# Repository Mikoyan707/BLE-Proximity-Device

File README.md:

# ESP32-C3 BLE Proximity Device

A two-node Bluetooth Low Energy (BLE) proximity detection system based on the **ESP32-C3**, designed to detect when two dedicated devices come within a defined proximity range.

The project combines a custom-designed PCB with ESP32-C3 BLE communication and an RSSI-based proximity detection algorithm. Each device continuously scans for its counterpart and uses the received BLE signal strength to determine whether the other device has entered the configured proximity region.

> **Project Status:** Hardware design completed. Firmware development, RSSI calibration, and physical testing are in progress.

---

## Overview

The system consists of two identical BLE-enabled devices.

Each device:

1. Advertises its BLE identity.
2. Continuously scans for the corresponding device.
3. Detects the other device when its BLE advertisement is received.
4. Measures the received signal strength indicator (RSSI).
5. Filters the RSSI measurements to reduce short-term fluctuations.
6. Applies a configurable proximity threshold.
7. Activates the local output when the other device enters the defined proximity region.

The system is intended to operate without requiring a smartphone or external gateway.

### Basic Concept

```text
             BLE Proximity Link

        Device A                 Device B
     ┌─────────────┐          ┌─────────────┐
     │ ESP32-C3    │          │ ESP32-C3    │
     │             │          │             │
     │ Advertise   │◄────────►│ Advertise   │
     │ Scan        │   BLE    │ Scan        │
     │ RSSI        │          │ RSSI        │
     │ Processing  │          │ Processing  │
     └──────┬──────┘          └──────┬──────┘
            │                        │
            ▼                        ▼
         Output                   Output
```

---

## Key Features

* Two-node standalone BLE proximity system
* ESP32-C3 based design
* BLE advertising and scanning
* Dedicated device identification
* RSSI-based proximity estimation
* RSSI filtering for improved stability
* Configurable proximity threshold
* Hysteresis-based proximity decision
* Custom PCB designed in KiCad
* CR2032 battery-powered hardware design
* 3.3 V regulated power supply
* Local LED/output indication
* Firmware structured for future expansion

---

## Hardware

The custom PCB is built around the **ESP32-C3-MINI-1-N4** module.

### Main Hardware

| Component             | Function                                        |
| --------------------- | ----------------------------------------------- |
| ESP32-C3-MINI-1-N4    | Main MCU and BLE controller                     |
| CR2032                | Battery supply                                  |
| AP2112K-3.3           | 3.3 V voltage regulator                         |
| LED                   | Proximity/status indication                     |
| Transistor stage      | LED/output driving                              |
| Push buttons          | User/control input                              |
| Decoupling capacitors | Power supply stabilization                      |
| Resistors             | Pull-ups, current limiting and transistor drive |

The complete schematic and PCB design are available in the [`hardware`](hardware/) directory.

---

## Hardware Design

### Schematic

The complete KiCad schematic is available at:

```text
hardware/schematic/
```

The repository will contain both the editable KiCad schematic and an exported version for easy viewing.

### PCB

The PCB has been designed specifically for the ESP32-C3 based proximity device.

```text
hardware/pcb/
```

The directory contains the editable PCB design and exported PCB views.

### 3D Design

3D renders of the PCB are provided in:

```text
hardware/3d/
```

These views are intended to document the physical board layout and component placement.

---

## Proximity Detection

The system uses **BLE RSSI** as an indicator of relative proximity.

A simplified detection pipeline is:

```text
BLE Advertisement
        │
        ▼
Device Identification
        │
        ▼
RSSI Measurement
        │
        ▼
RSSI Filtering
        │
        ▼
Proximity Decision
        │
    ┌───┴───┐
    ▼       ▼
   NEAR     FAR
    │       │
    ▼       ▼
 Output   Output
   ON       OFF
```

RSSI is not treated as an exact distance measurement because it is affected by antenna orientation, obstacles, multipath propagation, human-body absorption, and the surrounding environment.

Therefore, the project will use experimental calibration to determine a suitable operating threshold for the intended application.

---

## Firmware

Firmware development is currently in progress.

The planned firmware architecture consists of separate modules for:

```text
firmware/
├── src/
│   ├── main.cpp
│   ├── ble_proximity.cpp
│   ├── ble_proximity.h
│   ├── proximity.cpp
│   ├── proximity.h
│   ├── led.cpp
│   ├── led.h
│   └── config.h
│
└── platformio.ini
```

The firmware will progressively implement:

* GPIO initialization
* Output/LED control
* BLE advertising
* BLE scanning
* Device identification
* RSSI acquisition
* RSSI filtering
* Proximity state detection
* Hysteresis
* Timing/debounce logic
* Final proximity indication

---

## RSSI Filtering

Raw RSSI measurements can fluctuate considerably even when two devices remain stationary.

For this reason, the firmware will process multiple RSSI measurements rather than making a proximity decision from a single sample.

The planned processing chain is:

```text
Raw RSSI
   │
   ▼
Filtering
   │
   ▼
Filtered RSSI
   │
   ▼
Threshold + Hysteresis
   │
   ▼
Proximity State
```

The filtering method and threshold values will be finalized after measurements are collected from the actual hardware.

---

## Calibration

The proximity threshold will be experimentally determined using the completed devices.

Measurements will be collected at different physical separations and under different orientations.

Example measurement format:

| Distance | RSSI |
| -------: | ---: |
|    0.5 m |  TBD |
|    1.0 m |  TBD |
|    1.5 m |  TBD |
|    2.0 m |  TBD |
|    3.0 m |  TBD |
|    4.0 m |  TBD |

These values will be replaced with measurements from the physical hardware.

Detailed calibration results will be documented in:

```text
documentation/RSSI_calibration.md
```

---

## Repository Structure

```text
ESP32-C3-BLE-Proximity/
│
├── README.md
├── LICENSE
│
├── hardware/
│   ├── schematic/
│   ├── pcb/
│   ├── 3d/
│   └── fabrication/
│
├── firmware/
│   ├── src/
│   └── test/
│
├── documentation/
│
├── images/
│
└── results/
```

---

## Development Roadmap

### Hardware

* [ ] Schematic design
* [ ] PCB layout
* [ ] 3D PCB design/review
* [ ] PCB fabrication
* [ ] Physical hardware assembly
* [ ] Hardware validation

### Firmware

* [ ] GPIO test
* [ ] BLE advertising
* [ ] BLE scanning
* [ ] Device identification
* [ ] RSSI measurement
* [ ] RSSI filtering
* [ ] Proximity threshold
* [ ] Hysteresis
* [ ] LED/output control
* [ ] Two-device testing
* [ ] Final firmware optimization

### Documentation

* [ ] Initial hardware documentation
* [ ] Firmware architecture
* [ ] BLE protocol documentation
* [ ] RSSI calibration
* [ ] Experimental results
* [ ] Final performance analysis

---

## Limitations

The primary proximity estimation method is based on BLE RSSI.

RSSI-based proximity estimation does not provide a universally accurate physical distance because the measured signal strength depends on the environment and device orientation.

Potential sources of variation include:

* Antenna orientation
* Obstacles
* Human-body effects
* Multipath propagation
* Reflections
* Transmit power
* Device-to-device orientation
* Environmental RF interference

The final operating threshold will therefore be selected experimentally rather than assuming a fixed RSSI-to-distance relationship.

---

## Future Improvements

Potential future developments include:

* Improved RSSI filtering
* Adaptive proximity thresholds
* Low-power BLE operation
* Battery-life optimization
* Improved proximity-state stability
* Additional user feedback mechanisms
* Enclosure design
* More extensive environmental testing
* Multiple proximity zones
* Improved ranging techniques beyond basic RSSI

---

## Tools Used

* **KiCad** — Schematic and PCB design
* **ESP32-C3** — Embedded controller and BLE
* **PlatformIO / Arduino framework** — firmware development
* **Git / GitHub** — Version control and project documentation

---

## Project Status

This project is under active development.

The custom hardware design is being documented first, followed by firmware implementation, RSSI calibration, physical testing, and final performance evaluation.

---

## License

This project is released under the **MIT License**.

See `LICENSE` for details.

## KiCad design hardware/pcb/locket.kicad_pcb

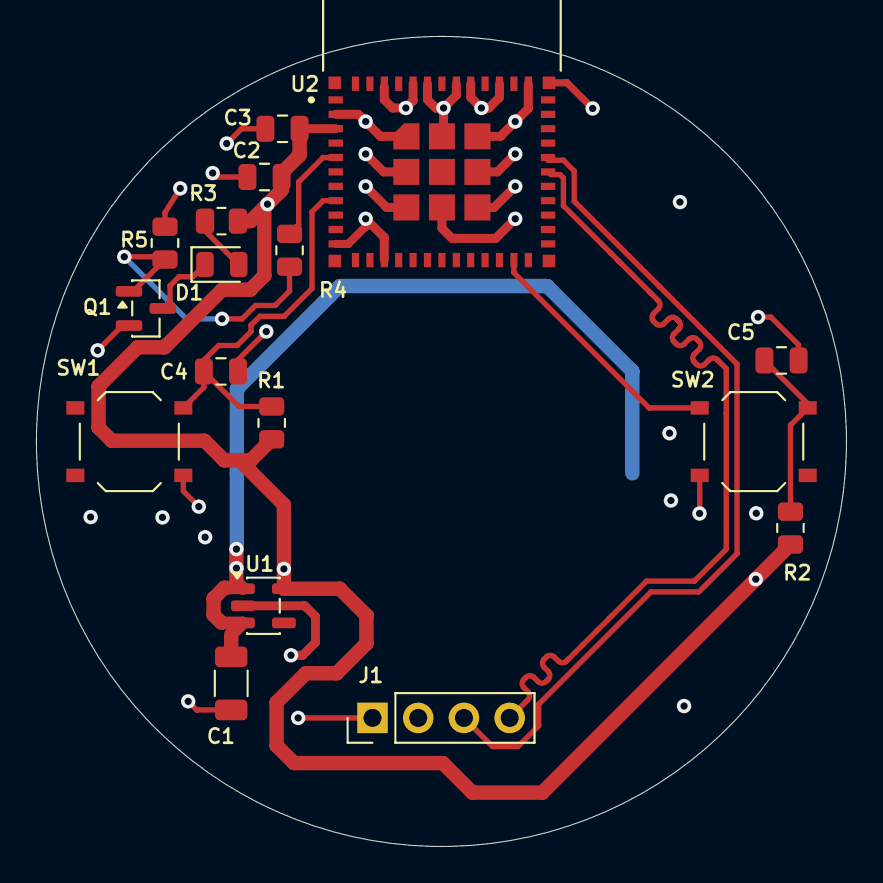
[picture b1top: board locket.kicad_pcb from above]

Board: 2 copper layers, 45.0 x 45.0 mm, 18 parts (1 on the bottom side), 11 nets.

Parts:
BT1: LIR2032; BatteryHolder_Keystone_3034_1x20mm
C1: 47uF; C_1206_3216Metric
C2: 10uF; C_0805_2012Metric
C3: 0.1uF; C_0805_2012Metric
C4, C5: 1uF; C_0805_2012Metric
D1: LED; LED_0805_2012Metric
J1: PinHeader_1x04_P2.54mm_Vertical
Q1: SOT-23
R1, R2, R4, R5: 10kohm; R_0805_2012Metric
R3: 330ohm; R_0805_2012Metric
SW1, SW2: SW_Push; SW_Push_1P1T_XKB_TS-1187A
U1: AP2112K-3.3; SOT-23-5
U2: ESP32-C3-MINI-1-N4; XCVR_ESP32-C3-MINI-1-N4

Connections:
+3.3V: C2.1, C3.1, R1.1, R2.1, R3.1, U1.5 (VOUT), U2.3 (3V3)
GND: BT1.2 (-), C1.2, C2.2, C3.2, C4.2, C5.2, J1.1, Q1.2 (S), R5.2, SW1.2, SW2.2, U1.2 (GND), U2.1 (GND), U2.2 (GND), U2.11 (GND), U2.14 (GND), U2.36 (GND), U2.37 (GND), U2.38 (GND), U2.39 (GND), U2.40 (GND), U2.41 (GND), U2.42 (GND), U2.43 (GND), U2.44 (GND), U2.45 (GND), U2.46 (GND), U2.47 (GND), U2.48 (GND), U2.49_1 (GND), U2.49_2 (GND), U2.49_3 (GND), U2.49_4 (GND), U2.49_5 (GND), U2.49_6 (GND), U2.49_7 (GND), U2.49_8 (GND), U2.49_9 (GND), U2.50 (GND), U2.51 (GND), U2.52 (GND), U2.53 (GND)
unnamed: BT1.1 (+), C1.1, U1.1 (VIN), U1.3 (EN)
unnamed: D1.2 (A), R3.2
unnamed: D1.1 (K), Q1.3 (D)
unnamed: J1.3, U2.31 (TXD0)
unnamed: J1.4, U2.30 (RXD0)
unnamed: Q1.1 (G), R4.1, R5.1
unnamed: C4.1, R1.2, SW1.1, U2.8 (EN)
unnamed: R4.2, U2.5 (IO2)
unnamed: C5.1, R2.2, SW2.1, U2.23 (IO9)
